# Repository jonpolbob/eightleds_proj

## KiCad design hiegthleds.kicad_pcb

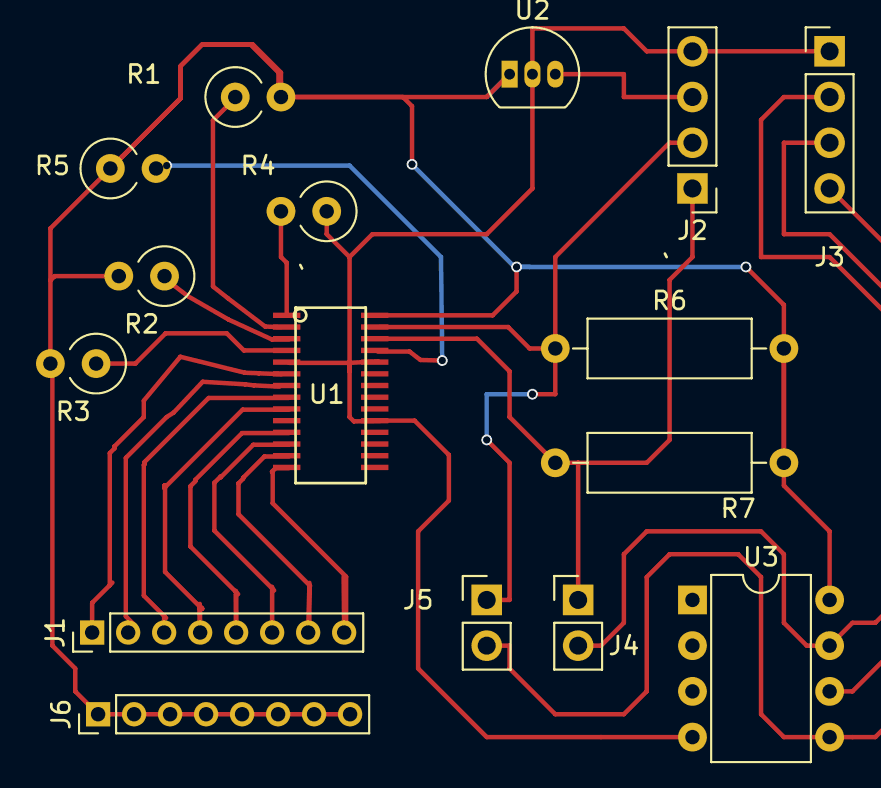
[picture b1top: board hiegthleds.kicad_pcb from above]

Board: 2 copper layers, 16 parts (0 on the bottom side), 21 nets.

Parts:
J1, J6: Conn_01x08; Socket_Strip_Straight_1x08_Pitch2.00mm
J2: Conn_01x04; Socket_Strip_Straight_1x04_Pitch2.54mm
J3: Conn_01x04; Pin_Header_Straight_1x04_Pitch2.54mm
J4, J5: Conn_01x02; Pin_Header_Straight_1x02_Pitch2.54mm
R1, R2, R3, R5: 10K; R_Axial_DIN0309_L9.0mm_D3.2mm_P2.54mm_Vertical
R4: 2k; R_Axial_DIN0309_L9.0mm_D3.2mm_P2.54mm_Vertical
R6: 4K7; R_Axial_DIN0309_L9.0mm_D3.2mm_P12.70mm_Horizontal
R7: 4K7R; R_Axial_DIN0309_L9.0mm_D3.2mm_P12.70mm_Horizontal
U1: PCA9955BTWJ; htssop-28
U2: L78L05_TO92; TO-92_Inline_Narrow_Oval
U3: ATTINY85-20PU; DIP-8_W7.62mm

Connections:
+5C: J6.1, J6.2, J6.3, J6.4, J6.5, J6.6, J6.7, J6.8, R1.2, R2.2, R3.2, R5.1, R6.2, R7.2, U1.28, U2.1, U3.8
+12P: J2.3, U2.3
GND: J2.4, J3.1, R4.1, U1.5, U1.19, U1.24, U2.2, U3.4
unnamed: J1.1, U1.6
unnamed: J1.2, U1.7
unnamed: J1.3, U1.8
unnamed: J1.4, U1.9
unnamed: J1.5, U1.11
unnamed: J1.6, U1.12
unnamed: J1.7, U1.13
unnamed: J1.8, U1.14
unnamed: J2.1, J4.1, R7.1, U1.26
unnamed: J2.2, J5.1, R6.1, U1.27
unnamed: J3.2, J4.2, U3.7
unnamed: J3.3, U3.6
unnamed: J3.4, J5.2, U3.5
unnamed: R1.1, U1.2
unnamed: R2.1, U1.3
unnamed: R3.1, U1.4
unnamed: R4.2, U1.1
unnamed: R5.2, U1.25

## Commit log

2017-09-06 premier commit du projet
2017-09-06 mise a jour pcb
2017-09-06 ajout de librairie schema
2017-09-06 ajout composant de librairie
